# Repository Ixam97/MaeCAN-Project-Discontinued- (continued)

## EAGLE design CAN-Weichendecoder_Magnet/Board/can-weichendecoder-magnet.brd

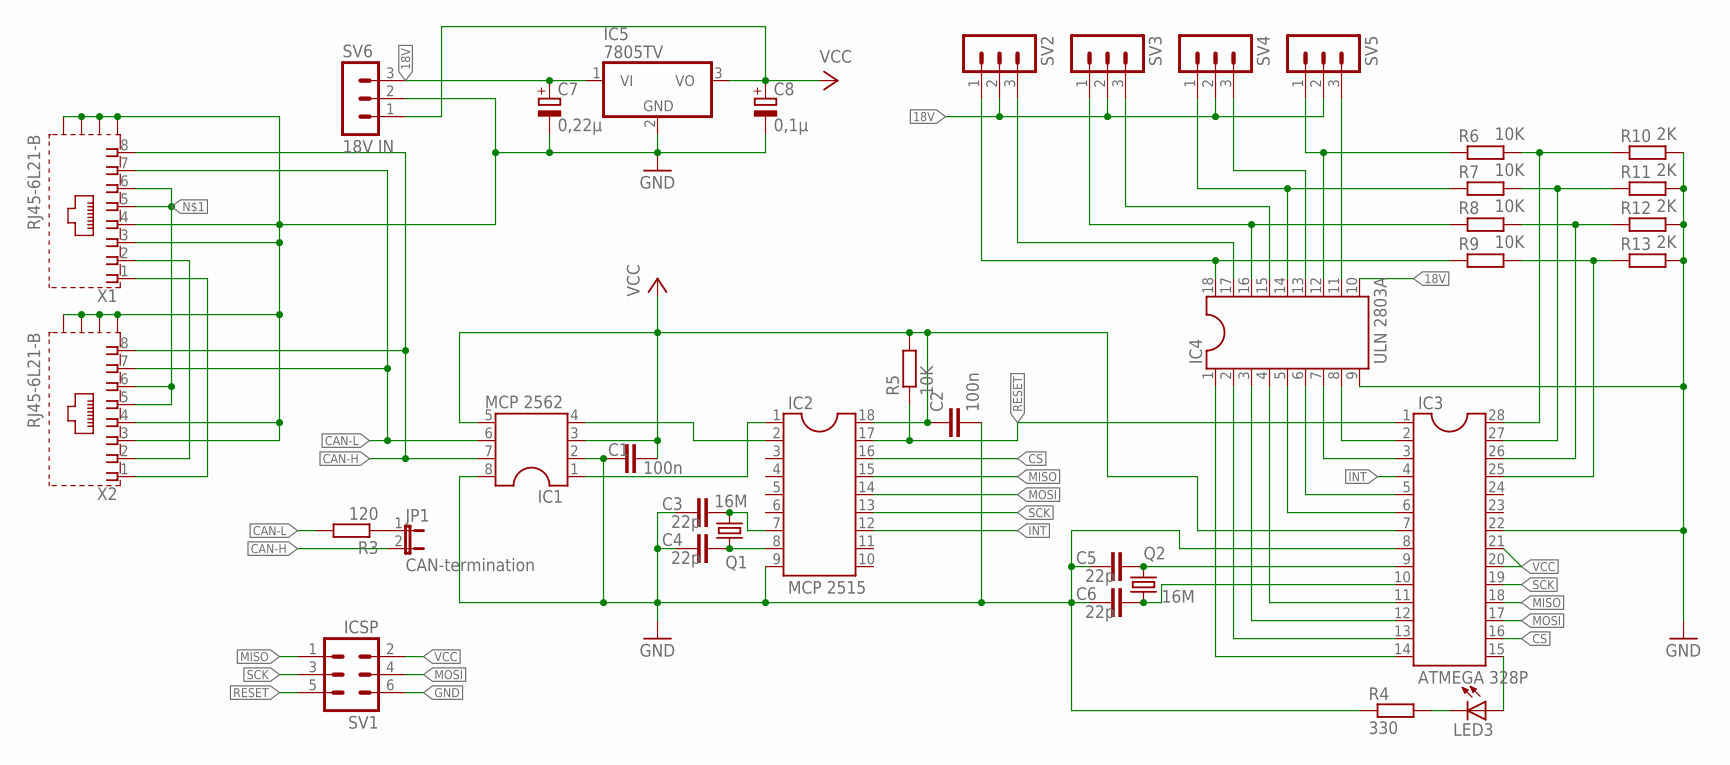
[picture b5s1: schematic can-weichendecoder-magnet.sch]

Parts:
C1, C2: 100n; C2.5-2
C3, C4, C5, C6: 22p; C2.5-2
C7: 0,22µ; E2,5-6
C8: 0,1µ; E2,5-6
IC1: MCP 2562; SOCKET-08
IC2: MCP 2515; SOCKET-18
IC3: ATMEGA 328P; DIL28-3
IC4: ULN 2803A; SOCKET-18
IC5: 7805TV; TO220V
JP1: CAN-termination; JP1
LED3: LED5MM
Q1, Q2: 16M; HC49/S
R3: 120; 0207/10
R4: 330; 0207/10
R5, R6, R7, R8, R9: 10K; 0207/10
R10, R11, R12, R13: 2K; 0207/10
SV1: ICSP; MA03-2
SV2, SV3, SV4, SV5: MA03-1
SV6: 18V IN; MA03-1
X1, X2: RJ45-6L21-B; RJ45-SHIELD1

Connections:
18V: C7.+, IC4.10, IC5.1 (VI), SV2.2, SV3.2, SV4.2, SV5.2, SV6.3
CAN-H: IC1.7, JP1.2, X1.8, X2.8
CAN-L: IC1.6, R3.2, X1.7, X2.7
CS: IC2.16, IC3.16
GND: C1.1, C2.2, C3.1, C4.1, C5.1, C6.1, C7.-, C8.-, IC1.2, IC1.8, IC2.9, IC3.8, IC3.22, IC4.9, IC5.2 (GND), R4.1, R10.2, R11.2, R12.2, R13.2, SV1.6, SV6.2, X1.3, X1.4, X1.S1 (S), X1.S2 (S), X1.S3 (S), X1.S4 (S), X2.3, X2.4, X2.S1 (S), X2.S2 (S), X2.S3 (S), X2.S4 (S)
INT: IC2.12, IC3.4
MISO: IC2.15, IC3.18, SV1.1
MOSI: IC2.14, IC3.17, SV1.4
unnamed: X1.5, X1.6, X2.5, X2.6
unnamed: IC1.4, IC2.2
unnamed: X1.2, X2.2
unnamed: C4.2, IC2.8, Q1.1
unnamed: JP1.1, R3.1
unnamed: C3.2, IC2.7, Q1.2
unnamed: C5.2, IC3.9, Q2.2
unnamed: C6.2, IC3.10, Q2.1
unnamed: IC1.1, IC2.1
unnamed: IC3.2, IC4.8
unnamed: IC3.3, IC4.7
unnamed: LED3.K (C), R4.2
unnamed: IC3.15, LED3.A
unnamed: IC3.5, IC4.6
unnamed: IC3.6, IC4.5
unnamed: IC3.11, IC4.4
unnamed: IC3.12, IC4.3
unnamed: IC3.13, IC4.2
unnamed: IC3.14, IC4.1
unnamed: IC4.18, R9.1, SV2.1
unnamed: IC4.17, SV2.3
unnamed: IC4.16, R8.1, SV3.1
unnamed: IC4.15, SV3.3
unnamed: IC4.14, R7.1, SV4.1
unnamed: IC4.13, SV4.3
unnamed: IC4.12, R6.1, SV5.1
unnamed: IC4.11, SV5.3
unnamed: IC3.28, R6.2, R10.1
unnamed: IC3.27, R7.2, R11.1
unnamed: IC3.26, R8.2, R12.1
unnamed: IC3.25, R9.2, R13.1
unnamed: X1.1, X2.1
RESET: IC2.17, IC3.1, R5.1, SV1.5
SCK: IC2.13, IC3.19, SV1.3
VCC: C1.2, C2.1, C8.+, IC1.3, IC1.5, IC2.18, IC3.7, IC3.20, IC3.21, IC5.3 (VO), R5.2, SV1.2, SV6.1

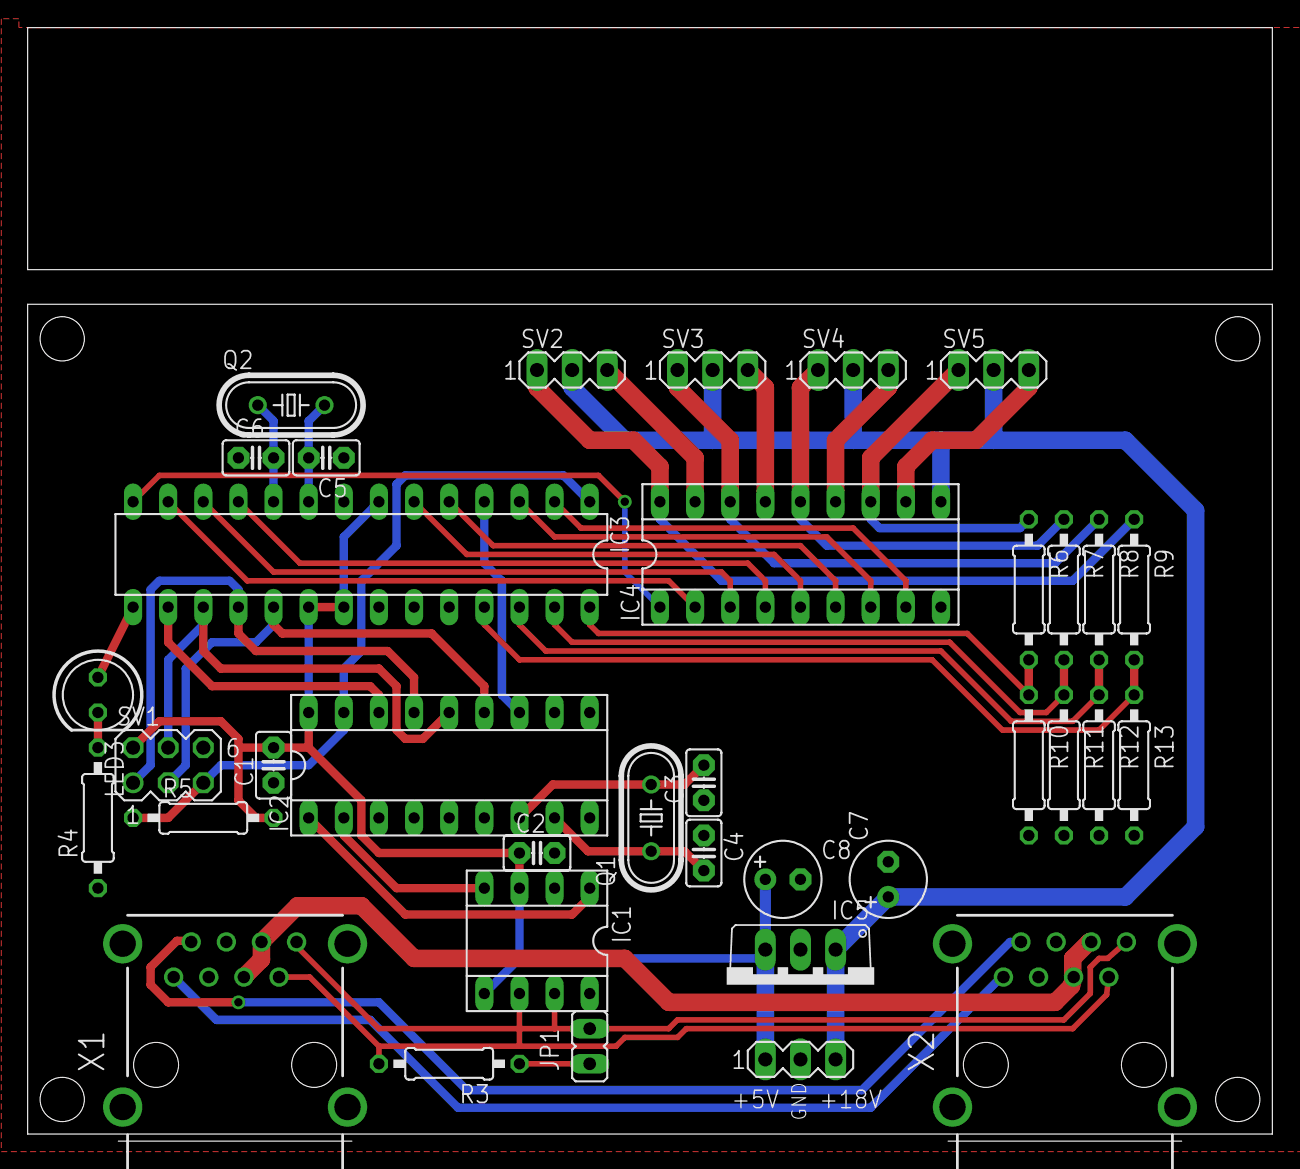
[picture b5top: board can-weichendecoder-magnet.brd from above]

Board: 2 copper layers, 90.0 x 80.5 mm, 36 parts (0 on the bottom side), 43 nets.

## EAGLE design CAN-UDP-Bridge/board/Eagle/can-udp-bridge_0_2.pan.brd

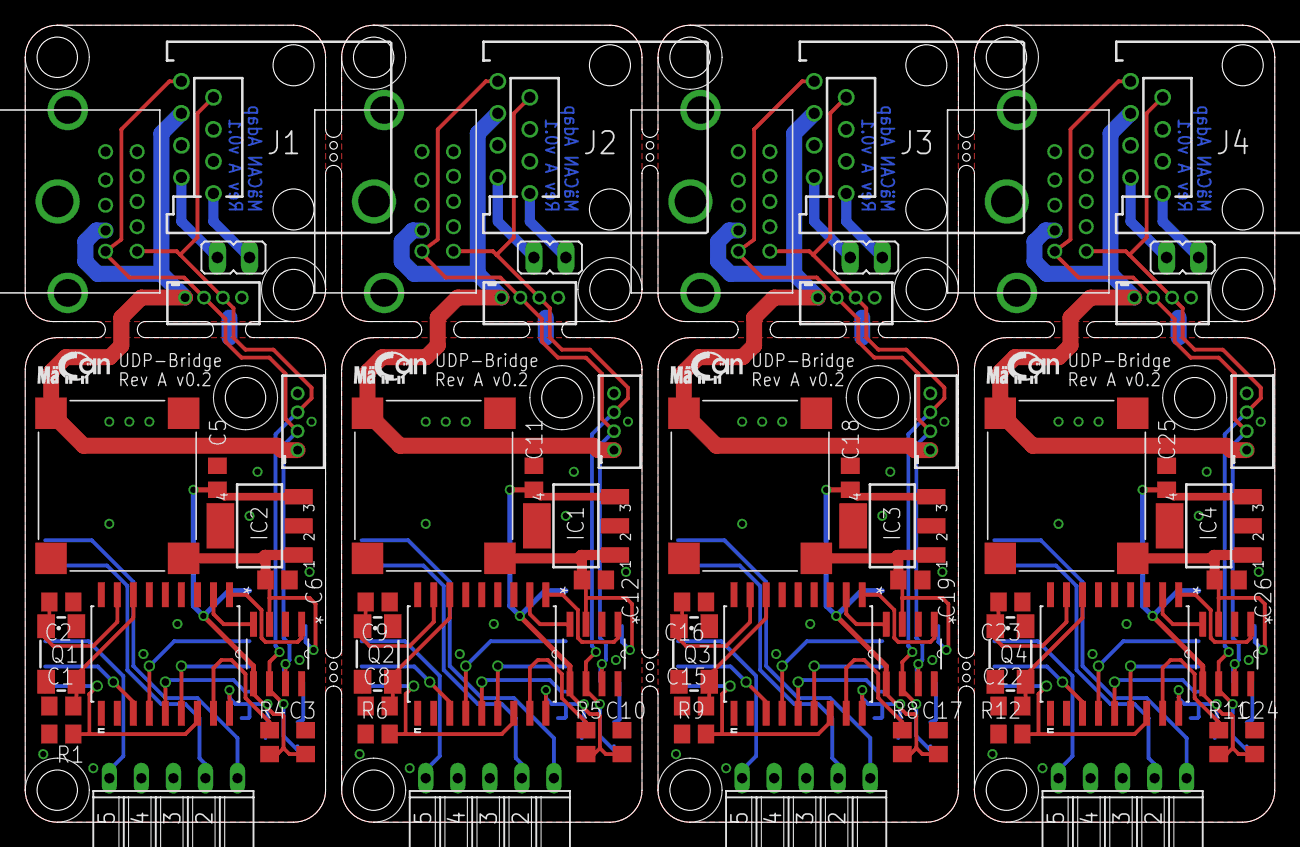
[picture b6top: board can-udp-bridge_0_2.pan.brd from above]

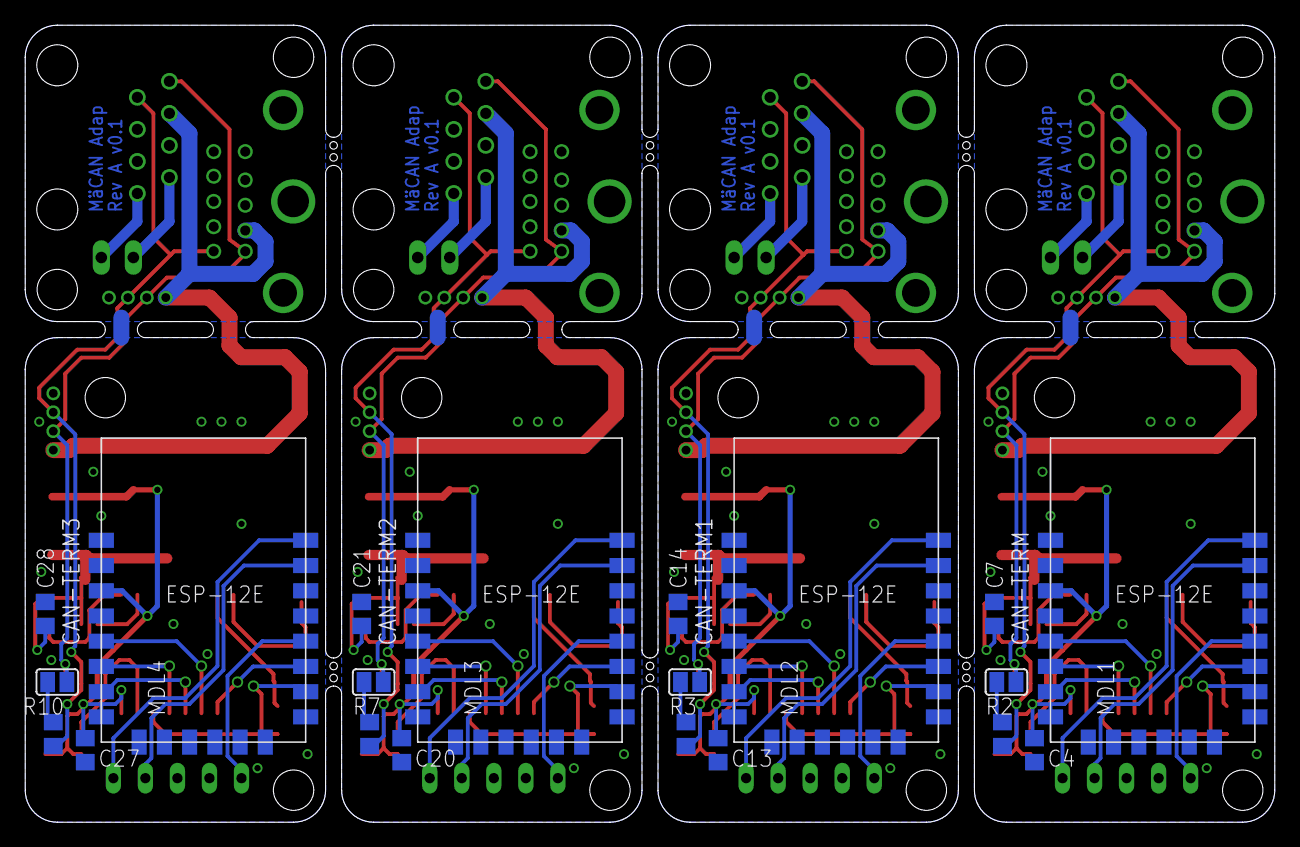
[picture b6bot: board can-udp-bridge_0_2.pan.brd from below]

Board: 2 copper layers, 99.1 x 63.2 mm, 92 parts (20 on the bottom side), 88 nets.

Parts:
C1, C2, C8, C9, C15, C16, C22, C23: 22p; C0805
C3, C4, C7, C10, C13, C14, C17, C20, C21, C24, C27, C28: 100n; C0805
C5, C6, C11, C12, C18, C19, C25, C26: 1µ; C0805
CAN-TERM, CAN-TERM1, CAN-TERM2, CAN-TERM3: SJ
IC1, IC2, IC3, IC4: MCP1703DB; SOT223
J1, J2, J3, J4: 215877-7
MDL1, MDL2, MDL3, MDL4: ESP8266-ESP12E
PROG, PROG1, PROG2, PROG3: FE05W
Q1, Q2, Q3, Q4: 16M; CTS406
R1, R4, R5, R6, R8, R9, R11, R12: 12k; R0805
R2, R3, R7, R10: 120R; R0805
TRACK, TRACK1, TRACK2, TRACK3: JP1
U$1, U$5, U$9, U$13: MCP2515-I/SO; SOIC127P1034X264-18N
U$2, U$6, U$10, U$14: MCP2562; SOIC127P600X175-8N
U$3, U$7, U$11, U$15: ROF-78E5.0-0.5SMD; ROF-78EXX-0.5SMD
U$4, U$8, U$12, U$16: MARKLIN-MD-10; MARKLIN-MD-10-PRINT
X1, X2, X3, X4, X5, X6, X7, X8: B4B-ZR

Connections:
+3V1: C10.1, C11.2, C13.2, IC1.3, MDL2.3, MDL2.8, R5.1, U$5.18, U$6.5
+3V2: C17.1, C18.2, C20.2, IC3.3, MDL3.3, MDL3.8, R8.1, U$9.18, U$10.5
+3V3: C3.1, C4.2, C5.2, IC2.3, MDL1.3, MDL1.8, R4.1, U$1.18, U$2.5
+3V4: C24.1, C25.2, C27.2, IC4.3, MDL4.3, MDL4.8, R11.1, U$13.18, U$14.5
+5V: C6.2, C7.1, IC2.1, U$2.3, U$3.3
+5V1: C12.2, C14.1, IC1.1, U$6.3, U$7.3
+5V2: C19.2, C21.1, IC3.1, U$10.3, U$11.3
+5V3: C26.2, C28.1, IC4.1, U$14.3, U$15.3
+18V: J1.6, U$3.1, U$4.1, X1.1, X3.1
+18V1: J2.6, U$7.1, U$8.1, X2.1, X4.1
+18V2: J3.6, U$11.1, U$12.1, X5.1, X6.1
+18V3: J4.6, U$15.1, U$16.1, X7.1, X8.1
CAN_H: CAN-TERM.1, J1.8, U$2.7, U$4.4, X1.2, X3.2
CAN_H1: CAN-TERM1.1, J2.8, U$6.7, U$8.4, X2.2, X4.2
CAN_H2: CAN-TERM2.1, J3.8, U$10.7, U$12.4, X5.2, X6.2
CAN_H3: CAN-TERM3.1, J4.8, U$14.7, U$16.4, X7.2, X8.2
CAN_L: J1.7, R2.1, U$2.6, U$4.8, X1.3, X3.3
CAN_L1: J2.7, R3.1, U$6.6, U$8.8, X2.3, X4.3
CAN_L2: J3.7, R7.1, U$10.6, U$12.8, X5.3, X6.3
CAN_L3: J4.7, R10.1, U$14.6, U$16.8, X7.3, X8.3
CS: MDL1.10, R1.1, U$1.16
CS1: MDL2.10, R6.1, U$5.16
CS2: MDL3.10, R9.1, U$9.16
CS3: MDL4.10, R12.1, U$13.16
GND: C1.2, C2.2, C3.2, C4.1, C5.1, C6.1, C7.2, IC2.2, J1.4, MDL1.9, PROG.3, PROG.4, R1.2, U$1.9, U$2.2, U$2.8, U$3.2, U$4.2, U$4.GND1, U$4.GND2, U$4.GND3, X1.4, X3.4
GND1: C8.2, C9.2, C10.2, C11.1, C12.1, C13.1, C14.2, IC1.2, J2.4, MDL2.9, PROG1.3, PROG1.4, R6.2, U$5.9, U$6.2, U$6.8, U$7.2, U$8.2, U$8.GND1, U$8.GND2, U$8.GND3, X2.4, X4.4
GND2: C15.2, C16.2, C17.2, C18.1, C19.1, C20.1, C21.2, IC3.2, J3.4, MDL3.9, PROG2.3, PROG2.4, R9.2, U$9.9, U$10.2, U$10.8, U$11.2, U$12.2, U$12.GND1, U$12.GND2, U$12.GND3, X5.4, X6.4
GND3: C22.2, C23.2, C24.2, C25.1, C26.1, C27.1, C28.2, IC4.2, J4.4, MDL4.9, PROG3.3, PROG3.4, R12.2, U$13.9, U$14.2, U$14.8, U$15.2, U$16.2, U$16.GND1, U$16.GND2, U$16.GND3, X7.4, X8.4
INT: MDL1.11, U$1.12
INT1: MDL2.11, U$5.12
INT2: MDL3.11, U$9.12
INT3: MDL4.11, U$13.12
unnamed: U$1.1, U$2.1
unnamed: U$1.2, U$2.4
unnamed: U$5.1, U$6.1
unnamed: MDL1.12, PROG.5
unnamed: U$5.2, U$6.4
unnamed: C8.1, Q2.3, U$5.7
unnamed: C9.1, Q2.1, U$5.8
unnamed: CAN-TERM1.2, R3.2
unnamed: MDL2.16, PROG1.1
unnamed: MDL2.15, PROG1.2
unnamed: J2.2, TRACK1.2
unnamed: J2.1, TRACK1.1
unnamed: C1.1, Q1.3, U$1.7
unnamed: C2.1, Q1.1, U$1.8
unnamed: CAN-TERM.2, R2.2
unnamed: MDL1.16, PROG.1
unnamed: MDL1.15, PROG.2
unnamed: J1.2, TRACK.2
unnamed: J1.1, TRACK.1
unnamed: R4.2, U$1.17
unnamed: R5.2, U$5.17
unnamed: MDL2.12, PROG1.5
unnamed: U$9.1, U$10.1
unnamed: U$9.2, U$10.4
unnamed: C15.1, Q3.3, U$9.7
unnamed: C16.1, Q3.1, U$9.8
unnamed: CAN-TERM2.2, R7.2
unnamed: MDL3.16, PROG2.1
unnamed: MDL3.15, PROG2.2
unnamed: J3.2, TRACK2.2
unnamed: J3.1, TRACK2.1
unnamed: R8.2, U$9.17
unnamed: MDL3.12, PROG2.5
unnamed: U$13.1, U$14.1
unnamed: U$13.2, U$14.4
unnamed: C22.1, Q4.3, U$13.7
unnamed: C23.1, Q4.1, U$13.8
unnamed: CAN-TERM3.2, R10.2
unnamed: MDL4.16, PROG3.1
unnamed: MDL4.15, PROG3.2
unnamed: J4.2, TRACK3.2
unnamed: J4.1, TRACK3.1
unnamed: R11.2, U$13.17
unnamed: MDL4.12, PROG3.5
SCK: MDL1.5, U$1.13
SCK1: MDL2.5, U$5.13
SCK2: MDL3.5, U$9.13
SCK3: MDL4.5, U$13.13
SI: MDL1.7, U$1.14
SI1: MDL2.7, U$5.14
SI2: MDL3.7, U$9.14
SI3: MDL4.7, U$13.14
SO: MDL1.6, U$1.15
SO1: MDL2.6, U$5.15
SO2: MDL3.6, U$9.15
SO3: MDL4.6, U$13.15

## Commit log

2016-04-07 Added files via upload
2016-04-08 Readme wird um eine Doku erweitert
2016-04-08 Anpassungen
2016-04-11 Mehr Kommentare hinzugefügt
2016-04-11 Schaltplan hochgeladen
2016-04-14 Kleine Änderungen und aufräumen (v0.1, Rev A)
2016-04-14 Angepasst an Hardwareänderungen
2016-04-15 Gerber-Files, V0.1, Rev A, Final
2016-04-19 Servodecoder V0.1 Rev A
2016-04-19 Software-Version 0.1
2016-04-20 Software-Version 0.2
2016-04-20 Software-Version 0.2.1
2016-04-20 Changelog hinzugefügt
2016-04-22 Software-Version 0.3
2016-04-23 aufgeräumt
2016-05-04 AccessPoint-Modus
2016-05-11 Software-Version 0.4
2016-05-11 Changelog V0.4
2016-05-11 Chane
2016-07-10 Schnittstelle angepasst an FT232RL.
2016-07-19 Sourcecode hinzugefügt
2016-10-17 Umfangreiche Erweiterungen
2016-11-08 Updated MCAN-Lib
2016-11-08 I²C-Anschluss gedreht, Namensschema geändert.
2016-11-08 Namensschema angepasst
2016-11-08 UDP-Bridge v0.2
2016-11-08 UDP-Bridege v0.2 Panelisiert
2016-11-08 Gerber Zip, .gitignore
2016-11-08 gitignore
2016-11-08 Änderungen ...
2016-11-08 Stecker hinzugefügt
2016-11-09 Magnetdecoder Update
2016-11-14 Updated MCAN-Library
    * Information für neue MCAN-Geräte (Relais, Stellpult & GBS)
    hinzugefügt.
    * neue Funktionen hinzugefügt:
    ** void statusResponse(CanDevice device, int chanel);
    ** uint16_t getadrs(uint16_t prot, uint16_t locid);
2016-11-14 Fix Weichendecoder Magnet
2016-11-14 Added MäCAN Relais
2016-11-14 fix change prot issue on CAN-Relais
2016-11-14 Add new MäCAN Addon: Stellpult
    * Added CAN-Input (Stellpult)
    * modify MCAN.cpp (sendAccessoryFrame) to send working Accessory
    commands
2016-11-14 adding DEBUG Option to Relais AddOn
2017-02-01 CAN-UDP-Monitor Update
2017-02-12 PCB-Production-Ready
2017-03-07 previews
2017-03-07 Prewiev
2017-03-07 Prewiews
2017-03-07 preview updated
2017-04-04 Servo 2017-03-01
2017-04-07 Servo_2017-04-07
2017-04-12 webinterface_1.png
2017-04-14 MäCAN-Server
2017-04-14 webinterface_2.png
2017-04-25 Cleaning Server ...
2017-04-25 Node.JS Server
2017-04-25 MaeCAN-Server.zip
2017-04-25 Install Script Update
2017-04-25 Install Script Update 2
2017-04-26 Updating...
2017-04-26 Updating again ...
2018-01-03 Versionsdatei
2020-04-29 Auf Eis gelegt
